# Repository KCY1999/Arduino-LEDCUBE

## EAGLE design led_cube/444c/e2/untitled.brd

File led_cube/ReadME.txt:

*The "Arduino main code.txt" is a file that is used for the "reset button" in the program. 
It is not necesarry, but if you want this button to work, you need to keep the text file with the .exe

*All necesarry information should be inside the .exe under "info" or you can use "contact".

Download link:
http://bit.ly/LED_CUBE_CODE_GENERATOR

UPDATES:

***16.03.2015***

1. Added function to change the time of already generated code. -This has a backside, if you use it to change the time of the code, the undo button will not work to undo the generated code until you delete all of it. Not really a problem, just something to be aware of.
2. Added function to open the Arduino program with hyperlink.

***19.03.2015***

Changed the label names from "columns" to "planes" to make the explanation of the cube more clear. Nothing else was done so the previous version is just as good, but with different labels of the planes.

***10.02.2016***

Added a folder with pre made patterns that are ready to upload and run on the LED cube.

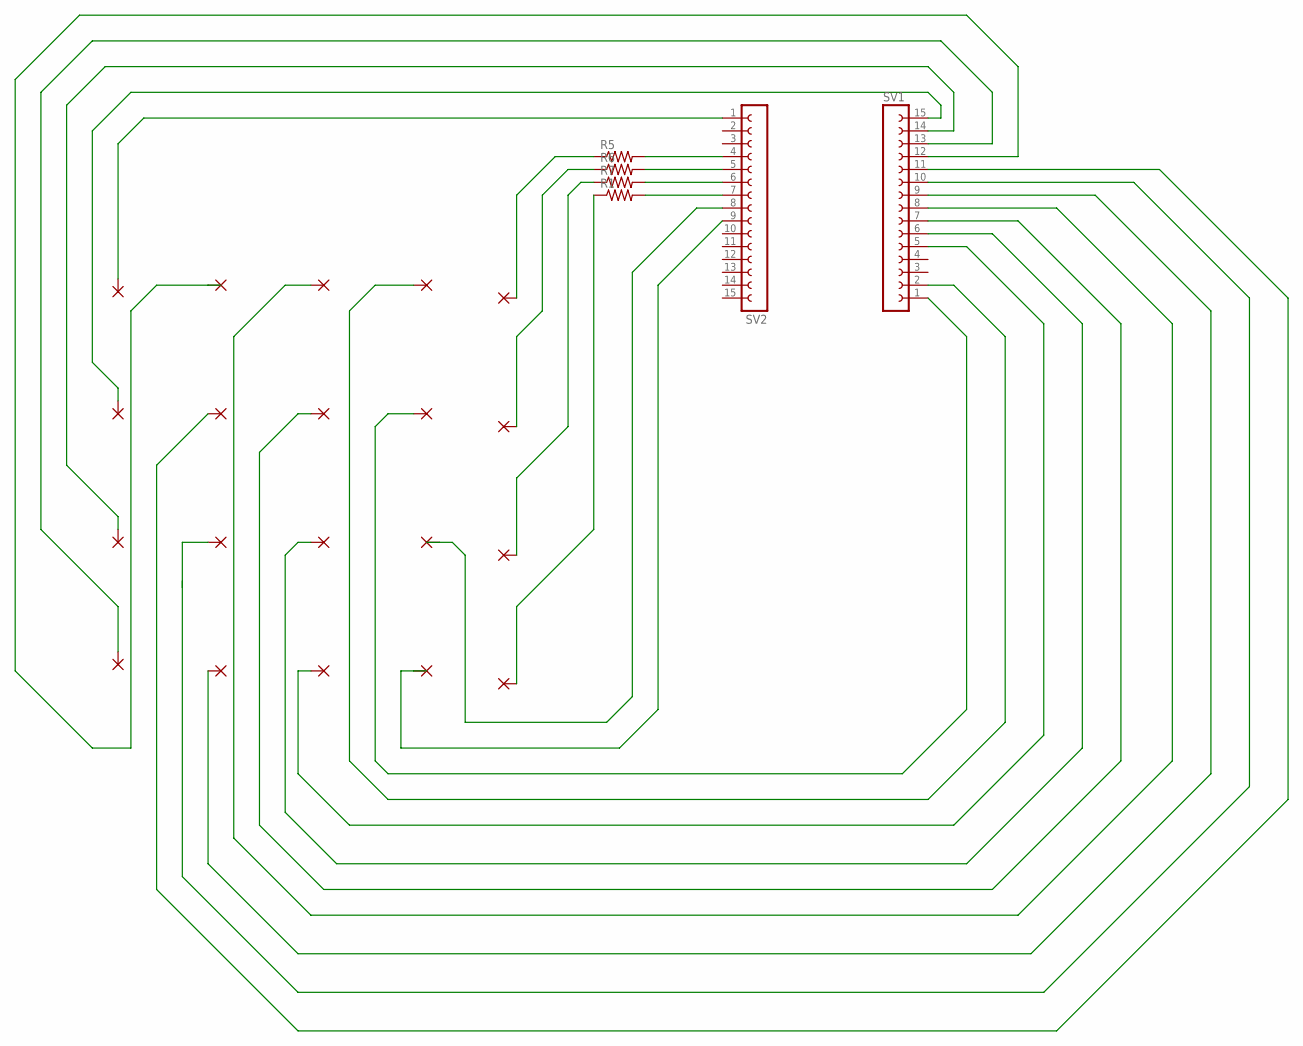
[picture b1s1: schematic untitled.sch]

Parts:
PAD1, PAD2, PAD3, PAD4, PAD5, PAD6, PAD7, PAD8, PAD9, PAD10, PAD11, PAD12, PAD13, PAD14, PAD15, PAD16, PAD17, PAD18, PAD19, PAD20: 1,6/0,8
R1, R5, R6, R7: FLIPFLOP-RES; 0805-THM
SV1, SV2: FE15-1; FE15

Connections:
unnamed: PAD17.1, SV2.1
unnamed: PAD19.1, SV1.14
unnamed: PAD18.1, SV1.15
unnamed: PAD20.1, SV1.13
unnamed: PAD16.1, SV1.12
unnamed: R5.2, SV2.4
unnamed: R6.2, SV2.5
unnamed: R7.2, SV2.6
unnamed: R1.2, SV2.7
unnamed: PAD6.1, SV1.1
unnamed: PAD7.1, SV2.8
unnamed: PAD8.1, SV2.9
unnamed: PAD5.1, SV1.2
unnamed: PAD12.1, SV1.5
unnamed: PAD9.1, SV1.8
unnamed: PAD11.1, SV1.6
unnamed: PAD10.1, SV1.7
unnamed: PAD15.1, SV1.9
unnamed: PAD14.1, SV1.10
unnamed: PAD1.1, R5.1
unnamed: PAD13.1, SV1.11
unnamed: PAD2.1, R6.1
unnamed: PAD3.1, R7.1
unnamed: PAD4.1, R1.1

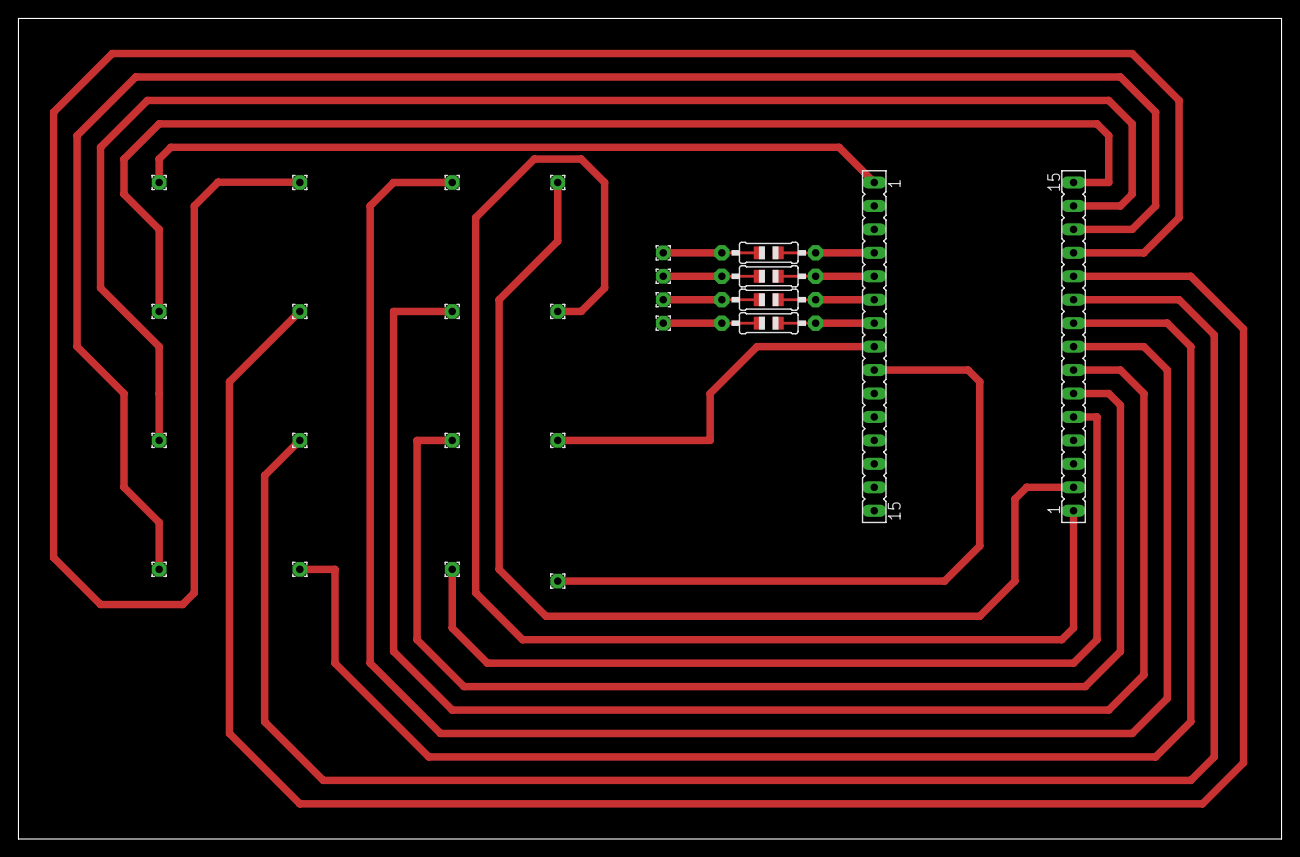
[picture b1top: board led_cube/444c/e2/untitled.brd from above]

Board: 2 copper layers, 136.8 x 88.9 mm, 26 parts (0 on the bottom side), 24 nets.

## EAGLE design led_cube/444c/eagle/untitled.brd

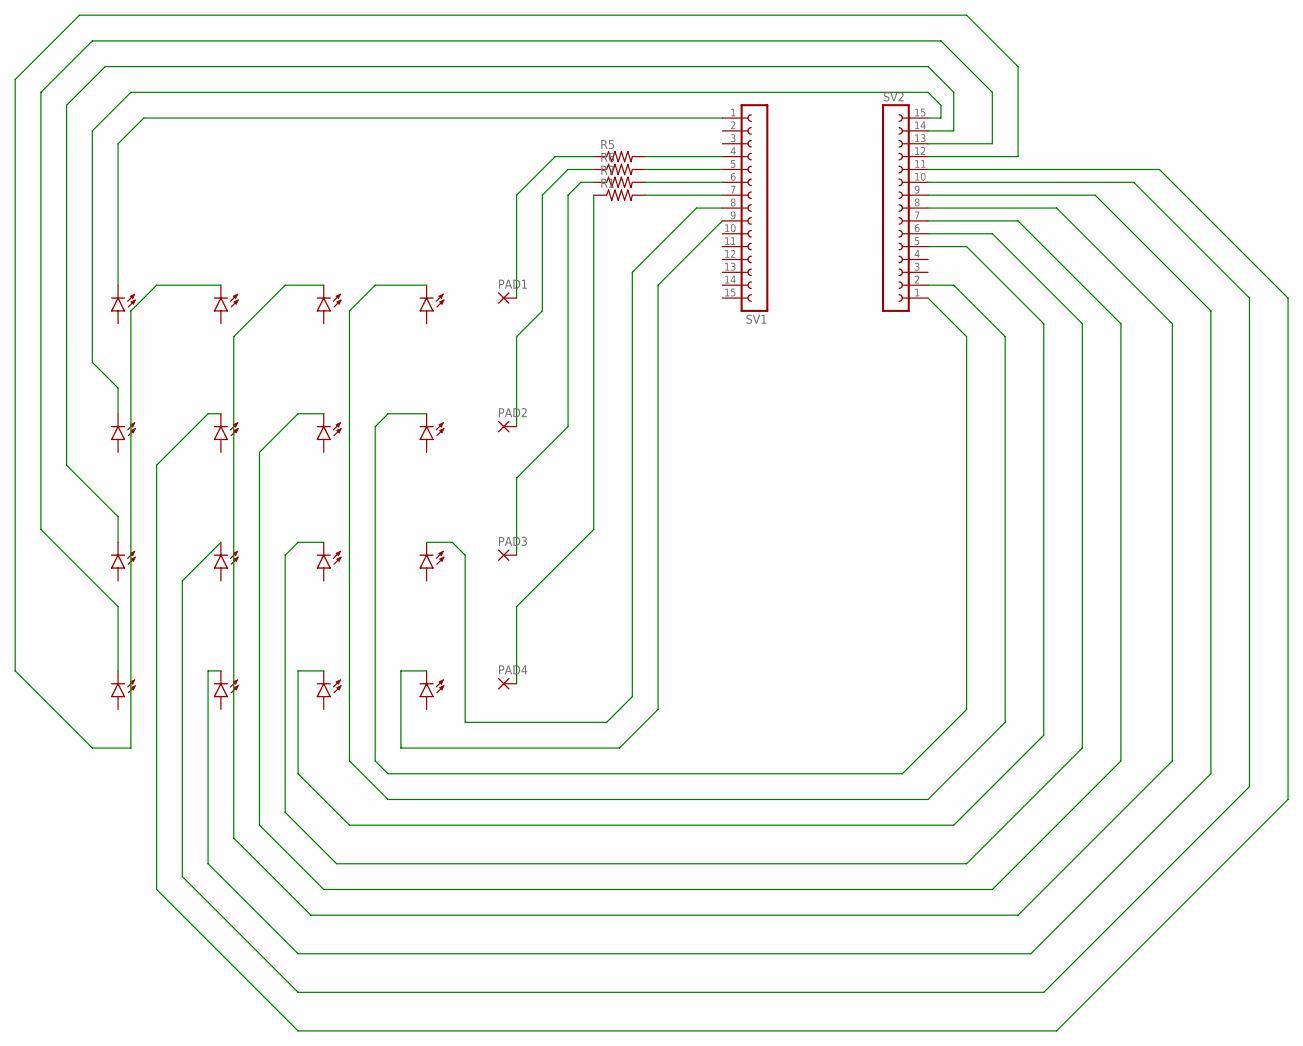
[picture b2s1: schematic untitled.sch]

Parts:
LED1, LED2, LED3, LED4, LED5, LED6, LED7, LED8, LED9, LED10, LED11, LED12, LED13, LED14, LED15, LED16: LAP4-BOTTOM; P47F-BOTTOM
PAD1, PAD2, PAD3, PAD4: 1,6/0,8
R1, R5, R6, R7: FLIPFLOP-RES; 0805-THM
SV1, SV2: FE15-1; FE15

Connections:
unnamed: LED12.C, SV1.1
unnamed: LED10.C, SV2.14
unnamed: LED11.C, SV2.15
unnamed: LED16.C, SV2.13
unnamed: LED9.C, SV2.12
unnamed: R5.2, SV1.4
unnamed: R6.2, SV1.5
unnamed: R7.2, SV1.6
unnamed: R1.2, SV1.7
unnamed: LED3.C, SV2.1
unnamed: LED1.C, SV1.8
unnamed: LED13.C, SV1.9
unnamed: LED5.C, SV2.2
unnamed: LED14.C, SV2.5
unnamed: LED6.C, SV2.8
unnamed: LED2.C, SV2.6
unnamed: LED4.C, SV2.7
unnamed: LED15.C, SV2.9
unnamed: LED7.C, SV2.10
unnamed: PAD1.1, R5.1
unnamed: LED8.C, SV2.11
unnamed: PAD2.1, R6.1
unnamed: PAD3.1, R7.1
unnamed: PAD4.1, R1.1

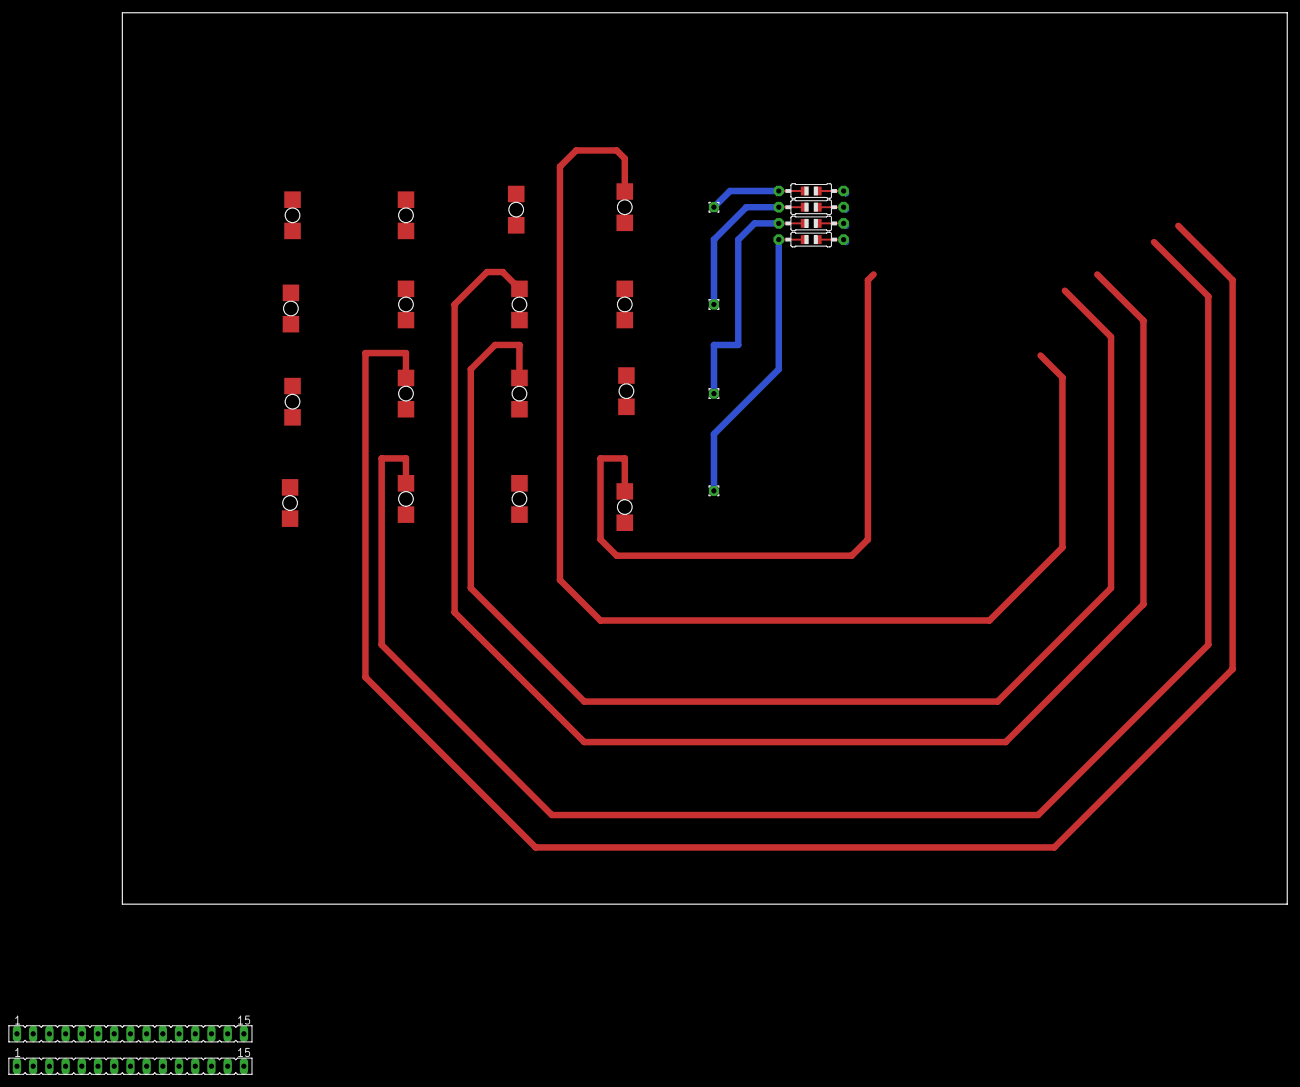
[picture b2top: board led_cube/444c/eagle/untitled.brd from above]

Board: 2 copper layers, 182.6 x 139.7 mm, 27 parts (0 on the bottom side), 24 nets.

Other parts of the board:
DRILEGEND: DRILEGEND

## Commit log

2021-10-10 4x4x4 LEDCUBE
